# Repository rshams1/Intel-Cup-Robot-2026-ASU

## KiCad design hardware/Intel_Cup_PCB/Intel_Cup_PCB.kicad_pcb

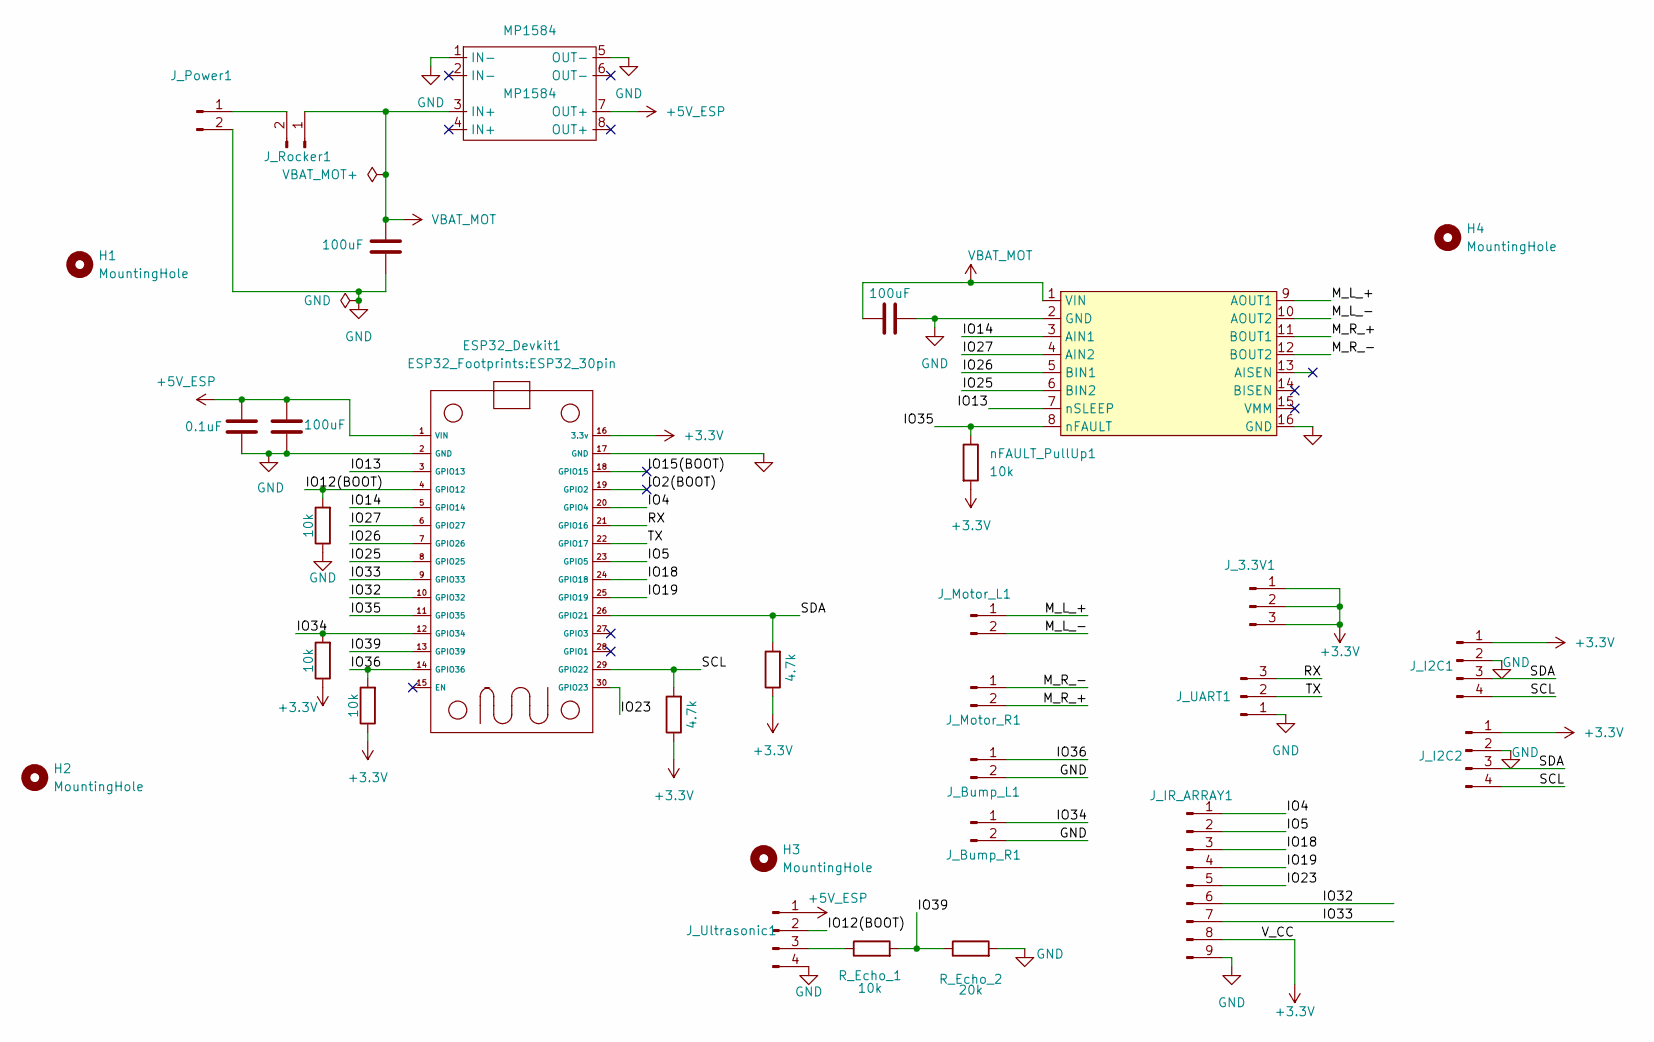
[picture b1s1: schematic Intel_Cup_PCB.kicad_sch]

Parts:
C2, C6, C7: 100uF; CP_Radial_D6.3mm_P2.50mm
C8: 0.1uF; C_Disc_D3.0mm_W1.6mm_P2.50mm
ESP32_Devkit1: ESP32_30pin
H1, H2, H3, H4: MountingHole; MountingHole_3.2mm_M3
J_3.3V1: Conn_01x03_Pin; PinHeader_1x03_P2.54mm_Vertical
J_Bump_L1: Conn_01x02_Pin; PinHeader_1x02_P2.54mm_Vertical
J_Bump_R1: Conn_01x02_Pin; PinHeader_1x02_P2.54mm_Vertical
J_I2C1, J_I2C2: PinSocket_1x04_P2.54mm_Vertical
J_IR_ARRAY1: Conn_01x09_Pin; PinHeader_1x09_P2.54mm_Vertical
J_Motor_L1: Conn_01x02_Pin; TerminalBlock_RND_205-00012_1x02_P5.00mm_Horizontal
J_Motor_R1: Conn_01x02_Pin; TerminalBlock_RND_205-00012_1x02_P5.00mm_Horizontal
J_Power1: Conn_01x02_Pin; TerminalBlock_RND_205-00012_1x02_P5.00mm_Horizontal
J_Rocker1: Conn_01x02_Pin; TerminalBlock_RND_205-00012_1x02_P5.00mm_Horizontal
J_UART1: PinSocket_1x03_P2.54mm_Vertical
J_Ultrasonic1: PinSocket_1x04_P2.54mm_Vertical
MP1584: MP1584; Untitled
R_Bump_L1: 10k; R_Axial_DIN0207_L6.3mm_D2.5mm_P7.62mm_Horizontal
R_Bump_R1: 10k; R_Axial_DIN0207_L6.3mm_D2.5mm_P7.62mm_Horizontal
R_Echo_1: 10k; R_Axial_DIN0207_L6.3mm_D2.5mm_P7.62mm_Horizontal
R_Echo_2: 20k; R_Axial_DIN0207_L6.3mm_D2.5mm_P7.62mm_Horizontal
R_SCL_DNP1: 4.7k; R_Axial_DIN0207_L6.3mm_D2.5mm_P7.62mm_Horizontal
R_SDA_DNP1: 4.7k; R_Axial_DIN0207_L6.3mm_D2.5mm_P7.62mm_Horizontal
R_Trig_Pulldown1: 10k; R_Axial_DIN0207_L6.3mm_D2.5mm_P7.62mm_Horizontal
U5: Polulu_DRV8833
nFAULT_PullUp1: 10k; R_Axial_DIN0207_L6.3mm_D2.5mm_P7.62mm_Horizontal

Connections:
+3.3V: ESP32_Devkit1.16 (3.3v), J_3.3V1.1, J_3.3V1.2, J_3.3V1.3, J_I2C1.1, J_I2C2.1, J_IR_ARRAY1.8, R_Bump_L1.1, R_Bump_R1.1, R_SCL_DNP1.1, R_SDA_DNP1.1, nFAULT_PullUp1.2
+5V_ESP: C7.1, C8.1, ESP32_Devkit1.1 (VIN), J_Ultrasonic1.1, MP1584.7 (OUT+)
/IO2(BOOT): ESP32_Devkit1.19 (GPIO2)
/IO4: ESP32_Devkit1.20 (GPIO4), J_IR_ARRAY1.1
/IO5: ESP32_Devkit1.23 (GPIO5), J_IR_ARRAY1.2
/IO12(BOOT): ESP32_Devkit1.4 (GPIO12), J_Ultrasonic1.2, R_Trig_Pulldown1.2
/IO13: ESP32_Devkit1.3 (GPIO13), U5.7 (nSLEEP)
/IO14: ESP32_Devkit1.5 (GPIO14), U5.3 (AIN1)
/IO15(BOOT): ESP32_Devkit1.18 (GPIO15)
/IO18: ESP32_Devkit1.24 (GPIO18), J_IR_ARRAY1.3
/IO19: ESP32_Devkit1.25 (GPIO19), J_IR_ARRAY1.4
/IO23: ESP32_Devkit1.30 (GPIO23), J_IR_ARRAY1.5
/IO25: ESP32_Devkit1.8 (GPIO25), U5.6 (BIN2)
/IO26: ESP32_Devkit1.7 (GPIO26), U5.5 (BIN1)
/IO27: ESP32_Devkit1.6 (GPIO27), U5.4 (AIN2)
/IO32: ESP32_Devkit1.10 (GPIO32), J_IR_ARRAY1.6
/IO33: ESP32_Devkit1.9 (GPIO33), J_IR_ARRAY1.7
/IO34: ESP32_Devkit1.12 (GPIO34), J_Bump_R1.1, R_Bump_R1.2
/IO35: ESP32_Devkit1.11 (GPIO35), U5.8 (nFAULT), nFAULT_PullUp1.1
/IO36: ESP32_Devkit1.14 (GPIO36), J_Bump_L1.1, R_Bump_L1.2
/IO39: ESP32_Devkit1.13 (GPIO39), R_Echo_1.2, R_Echo_2.1
/M_L_+: J_Motor_L1.1, U5.9 (AOUT1)
/M_L_-: J_Motor_L1.2, U5.10 (AOUT2)
/M_R_+: J_Motor_R1.2, U5.11 (BOUT1)
/M_R_-: J_Motor_R1.1, U5.12 (BOUT2)
/RX: ESP32_Devkit1.21 (GPIO16), J_UART1.3
/SCL: ESP32_Devkit1.29 (GPIO22), J_I2C1.4, J_I2C2.4, R_SCL_DNP1.2
/SDA: ESP32_Devkit1.26 (GPIO21), J_I2C1.3, J_I2C2.3, R_SDA_DNP1.2
/TX: ESP32_Devkit1.22 (GPIO17), J_UART1.2
GND: C2.2, C6.2, C7.2, C8.2, ESP32_Devkit1.2 (GND), ESP32_Devkit1.17 (GND), J_Bump_L1.2, J_Bump_R1.2, J_I2C1.2, J_I2C2.2, J_IR_ARRAY1.9, J_Power1.2, J_UART1.1, J_Ultrasonic1.4, MP1584.1 (IN-), MP1584.5 (OUT-), R_Echo_2.2, R_Trig_Pulldown1.1, U5.2 (GND), U5.16 (GND)
unnamed: J_Power1.1, J_Rocker1.2
unnamed: J_Ultrasonic1.3, R_Echo_1.1
VBAT_MOT: C2.1, C6.1, J_Rocker1.1, MP1584.3 (IN+), U5.1 (VIN)

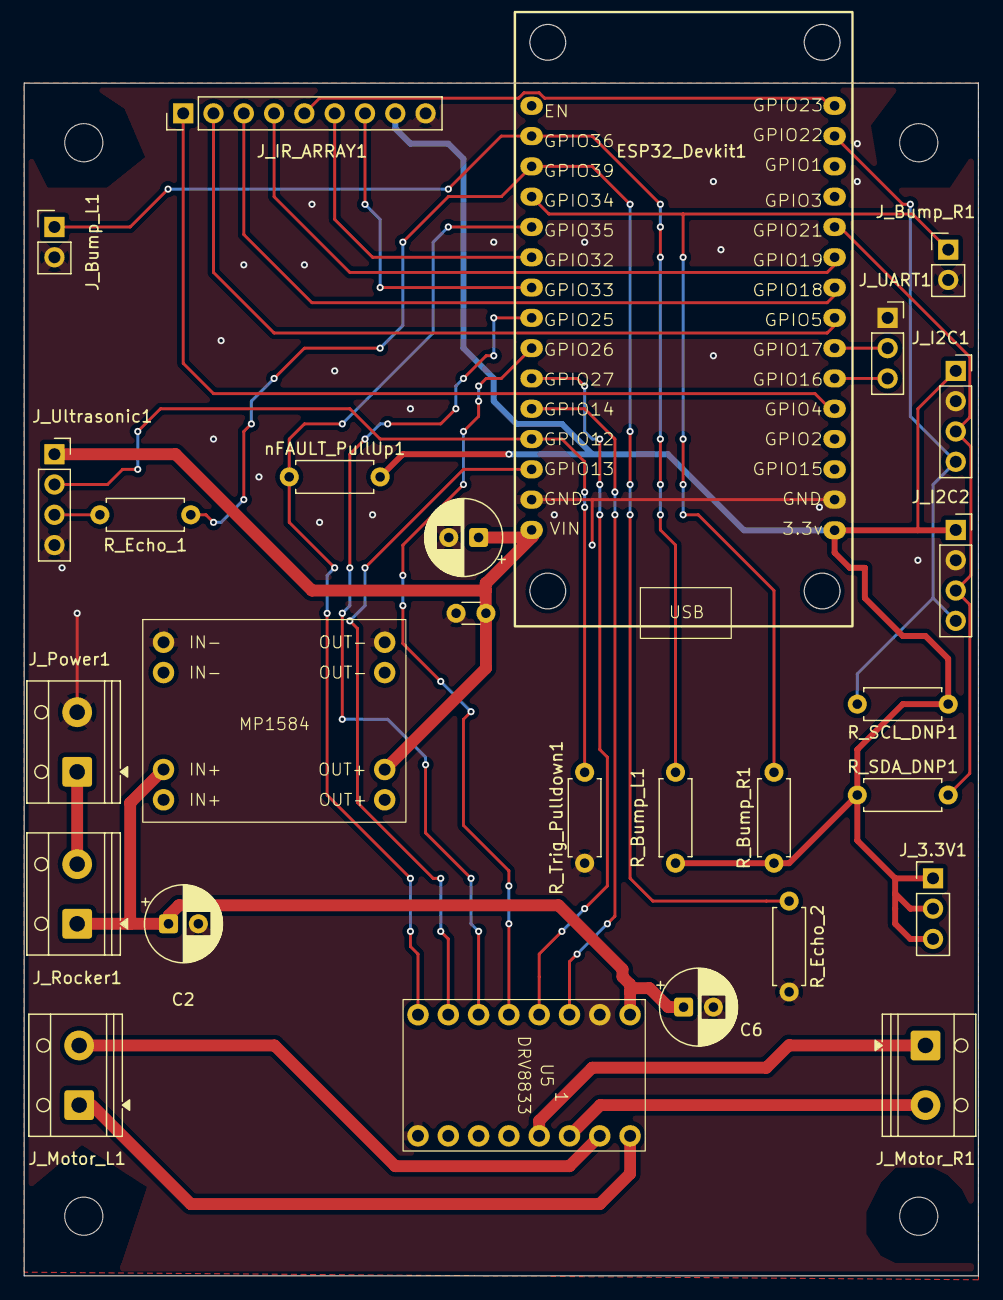
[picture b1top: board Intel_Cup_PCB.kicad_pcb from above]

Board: 2 copper layers, 80.0 x 104.9 mm, 31 parts (0 on the bottom side), 31 nets.

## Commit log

2026-05-01 Initial commit with KiCad hardware files
2026-05-10 Add symbol library and footprint library
2026-05-10 Added footprints for all components(might still need changing) and started PCB placement
2026-05-16 Placement before routing
2026-05-16 Updated placement, no extra pins
2026-05-16 Added ground plane
2026-05-18 Added new nets for MP1584 and fixed footprints
2026-05-21 Updated footprints
2026-05-26 Minor fixes
2026-06-01 Added bump sensor and distance sensor footprints
2026-06-05 Completed PCB with better ESP32 placement
